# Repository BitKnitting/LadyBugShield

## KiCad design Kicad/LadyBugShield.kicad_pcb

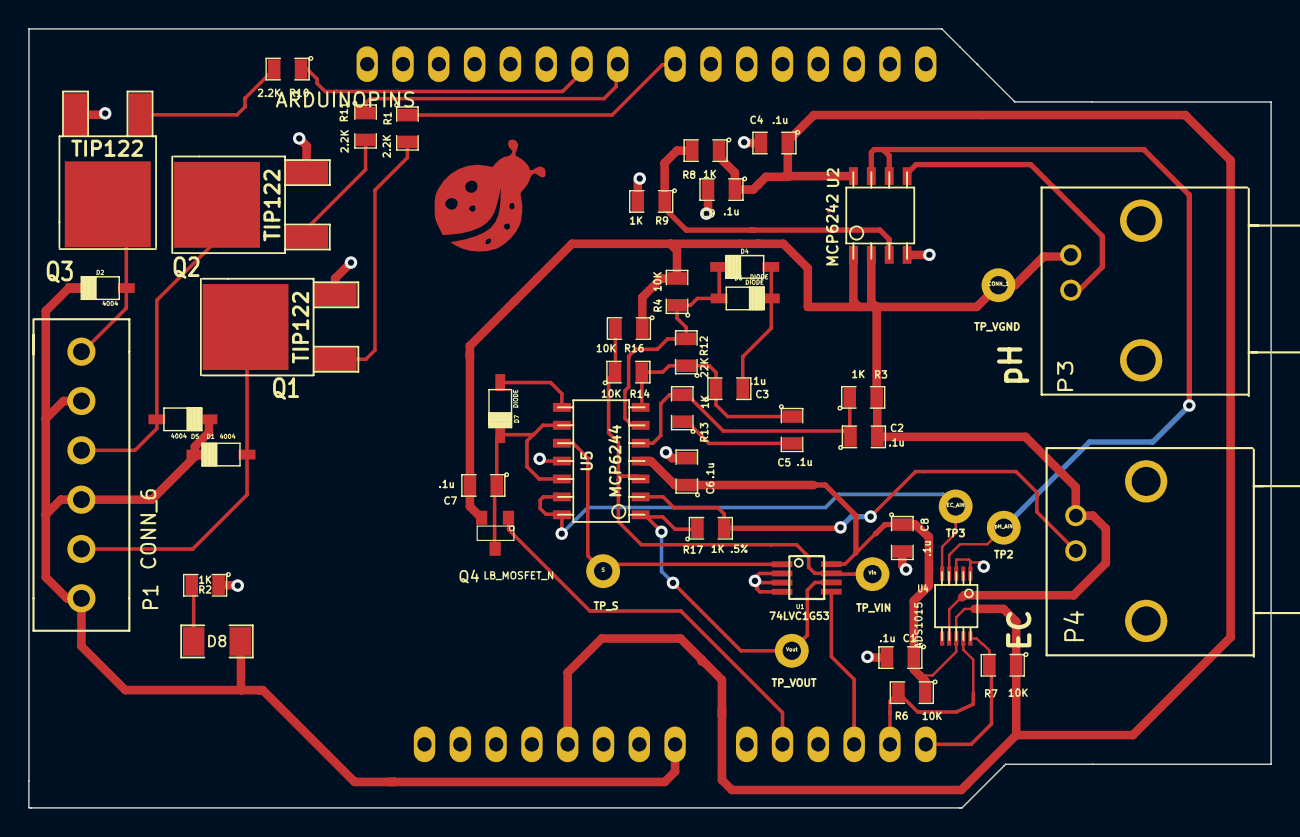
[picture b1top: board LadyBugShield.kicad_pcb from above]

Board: 2 copper layers, 88.1 x 55.3 mm, 49 parts (0 on the bottom side), 33 nets.

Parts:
ARD1: ARDUINOPINS; ArduinoLettuceBuddy
C1, C2, C3, C4, C5, C6, C7, C8, C9: .1u; SM0805
D1, D2, D5: 4004; SOD-123
D4, D6, D7: DIODE; SOD-123
D8: LED; SM1206
P1: CONN_6; LB_CONN_6
P3, P4: BNC; LB_BNC
Q1, Q2, Q3: TIP122; DPAK2
Q4: LB_MOSFET_N; LB_MOSFET
R1, R10, R11: 2.2K; SM0805
R2, R3, R8, R9, R13: 1K; SM0805
R4, R6, R7, R14, R16: 10K; SM0805
R12: 22K; SM0805
R17: 1K .5%; SM0805
TP2: pH_AIN; LB_TestPoint
TP3: EC_AIN; LB_TestPoint
TP_S: S; LB_TestPoint
TP_VGND: CONN_1; LB_TestPoint
TP_VIN: Vin; LB_TestPoint
TP_VOUT: Vout; LB_TestPoint
U1: 74LVC1G53; LB_TSSOP8
U2: MCP6242; so-8
U4: ADS1015; msoic-10
U5: MCP6244; LB_MCP6244

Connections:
/Arduino/12V: ARD1.4, D1.2, D2.2, D5.2, D8.1, P1.1, P1.3, P1.5
/Arduino/FET_pin: ARD1.6, Q4.G
/Arduino/MUX_out_pin: ARD1.8, U1.5
/Arduino/SCL: ARD1.10, R7.2, U4.10
/Arduino/SDA: ARD1.9, R6.2, U4.9
/Arduino/pump1_pin: ARD1.18, R1.1
/Arduino/pump2_pin: ARD1.19, R11.1
/Arduino/pump3_pin: ARD1.20, R10.1
/DigitalAccess/EC_AIN: TP3.1, U4.5, U5.13, U5.14
/DigitalAccess/pH_AIN: TP2.1, U2.6, U2.7, U4.4
/EC/AC/EC_Vin: R14.1, R16.2, TP_VIN.1, U1.7, U5.3
/EC/AC/G1: C3.2, D4.1, D6.2
/EC/AC/W_Vin+: C2.1, R3.1, R13.2, U5.5
/EC/AC/W_Vin-: D4.2, D6.1, R4.1, R12.2, U5.6
/EC/AC/W_Vout: C3.1, C5.1, R12.1, R14.2, U5.7
/EC/AC/f1: C5.2, R13.1
/EC/ECGain/EC_Vout: R17.1, TP_VOUT.1, U1.6, U5.1
/EC/EC_ProbeIN: P4.1, R17.2, U5.2
/EC/Rectify/RVin-: C7.1, D7.2, Q4.D, U5.9, U5.12
/EC/Rectify/R_Vout: D7.1, U5.8
/EC/Rectify/Signal: TP_S.1, U1.1, U5.10
/Power/VGND_V+: R8.2, R9.1, U2.3
/Pumps/pump1: D1.1, P1.2, Q1.2
/Pumps/pump2: D5.1, P1.4, Q2.2
/Pumps/pump3: D2.1, P1.6, Q3.2
/pH/pH_ProbeIN: P3.1, U2.5
GND: ARD1.2, ARD1.3, C1.2, C4.2, C6.2, C8.2, C9.2, Q1.3, Q2.3, Q3.3, R2.1, R9.2, U1.2, U1.3, U1.4, U2.4, U4.1, U4.3, U5.11
unnamed: D8.2, R2.2
unnamed: Q1.1, R1.2
unnamed: Q2.1, R11.2
unnamed: Q3.1, R10.2
VGND: C2.2, C7.2, P3.2, P4.2, Q4.S, R3.2, R4.2, R16.1, TP_VGND.1, U2.1, U2.2, U4.7
Vclean: ARD1.1, C1.1, C4.1, C6.1, C8.1, C9.1, R6.1, R7.1, R8.1, U1.8, U2.8, U4.8, U5.4

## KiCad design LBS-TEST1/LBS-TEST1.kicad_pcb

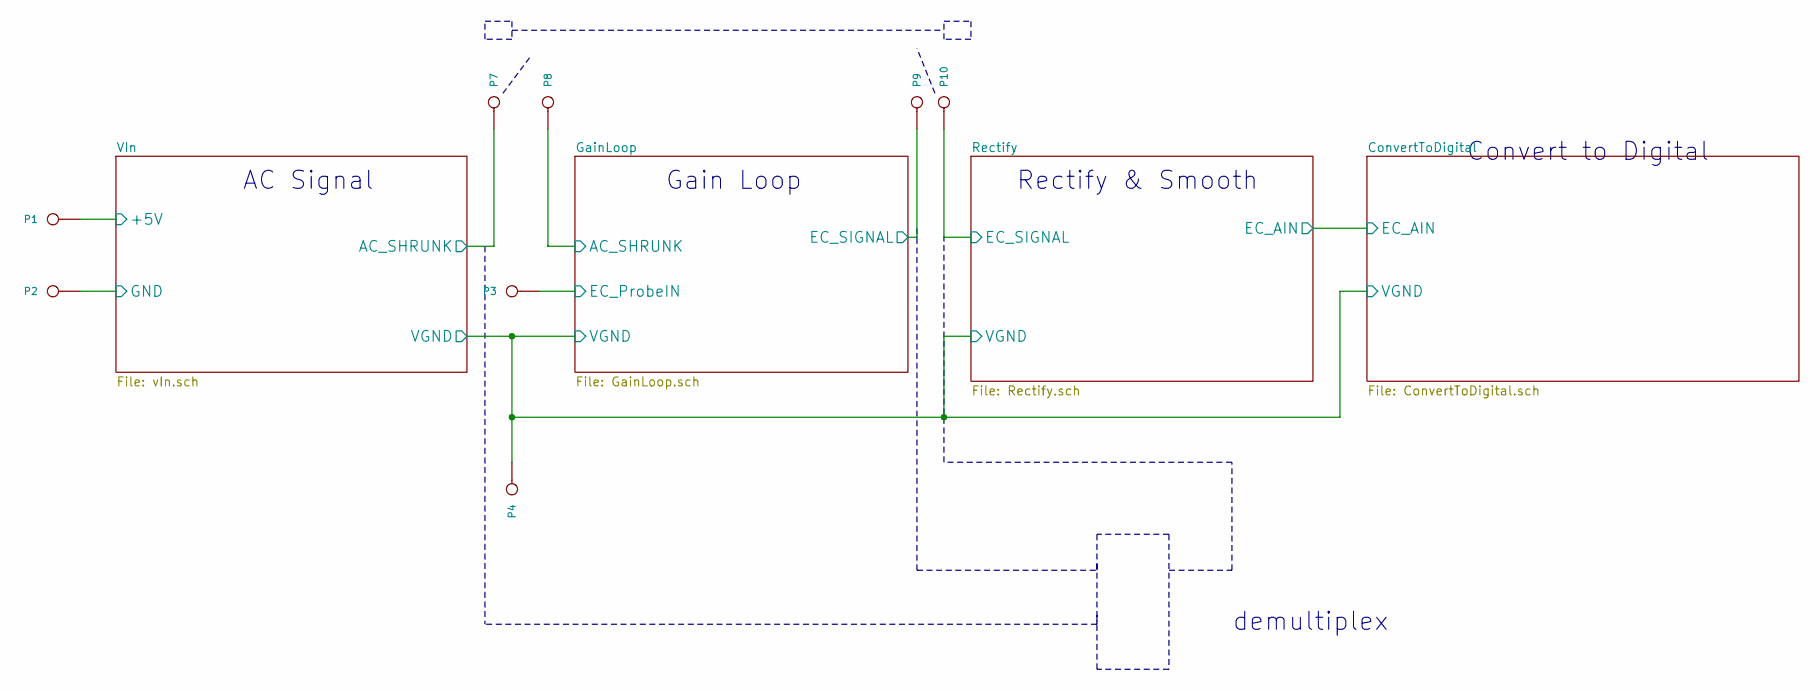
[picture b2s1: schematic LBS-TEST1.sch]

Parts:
P1, P2, P3, P4, P7, P8, P9, P10: CONN_1

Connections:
5+V: P1.1; also elsewhere on the board
/ConvertToDigital/VGND: P4.1; also elsewhere on the board
/GainLoop/AC_SHRUNK: P8.1; also elsewhere on the board
/GainLoop/EC_ProbeIN: P3.1; also elsewhere on the board
/GainLoop/EC_SIGNAL: P9.1; also elsewhere on the board
/Rectify/EC_SIGNAL: P10.1; also elsewhere on the board
/VIn/AC_SHRUNK: P7.1; also elsewhere on the board
PGND: P2.1; also elsewhere on the board

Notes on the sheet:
AC Signal
Gain Loop
Rectify & Smooth
Convert to Digital
demultiplex

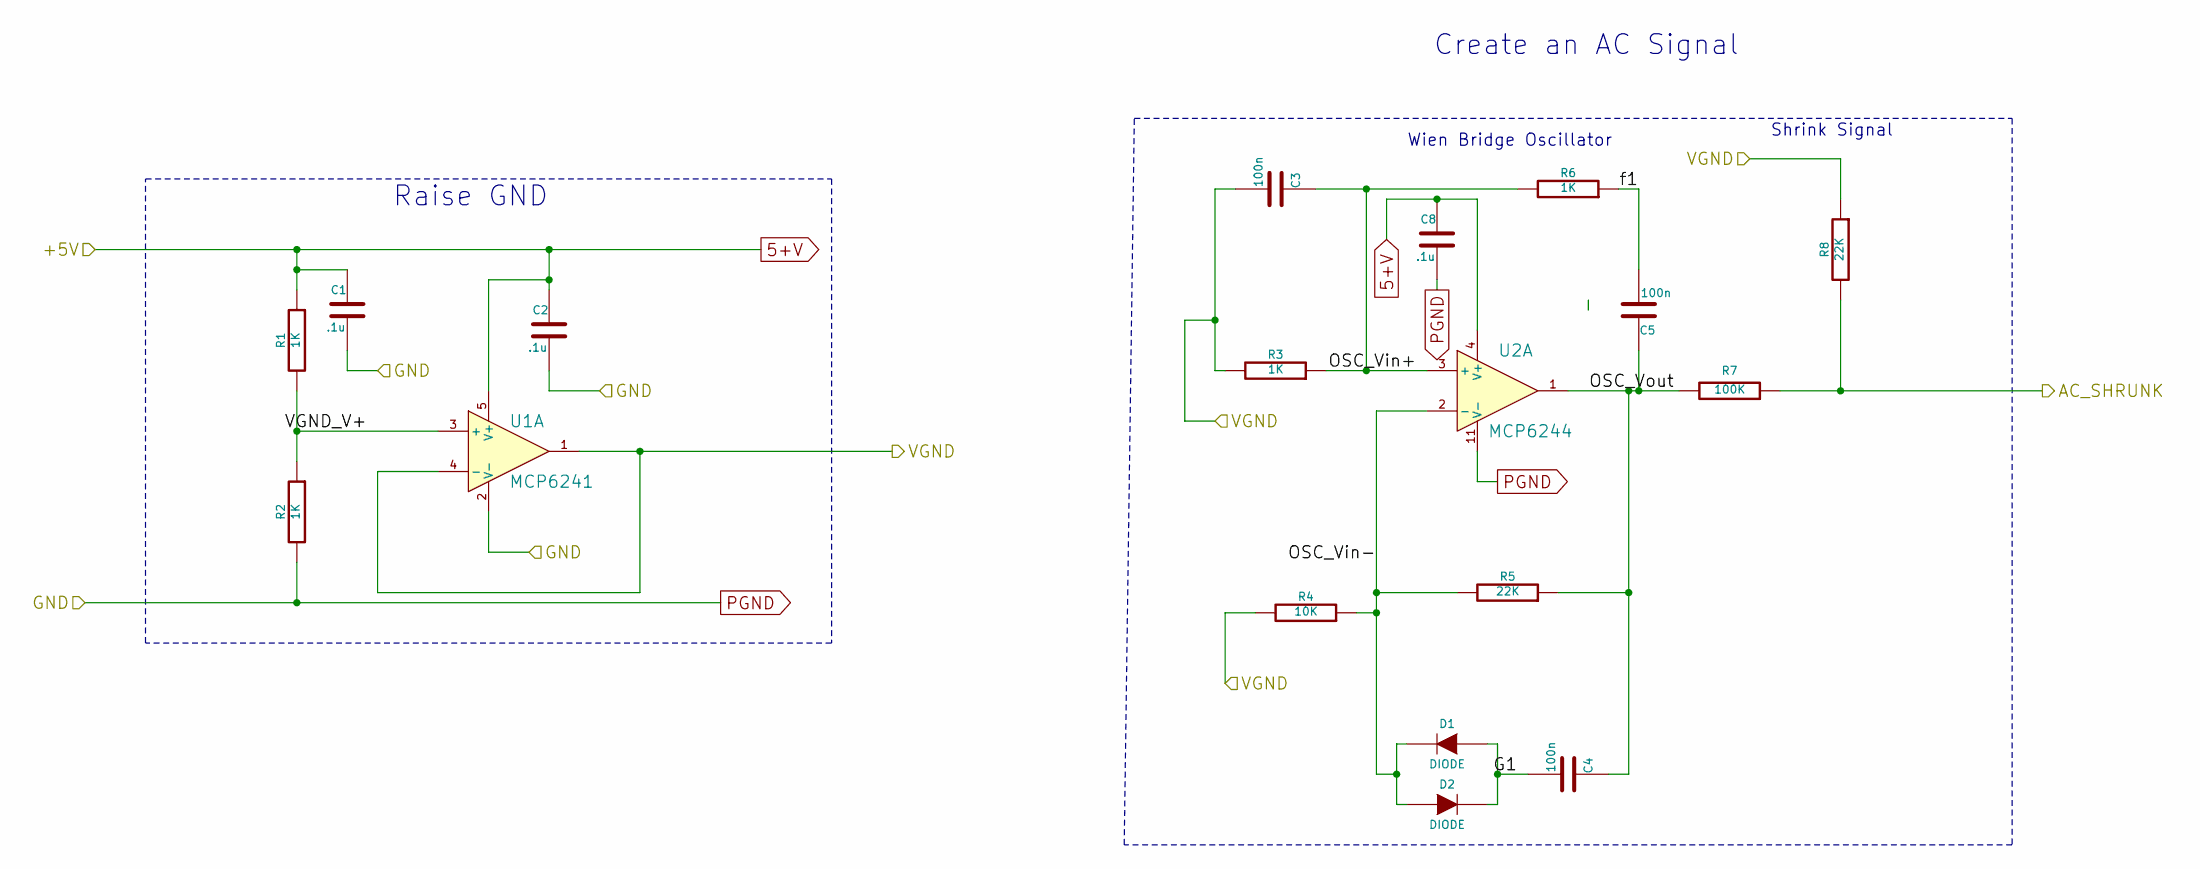
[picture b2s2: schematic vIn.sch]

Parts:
C1, C2, C8: .1u
C3, C4, C5: 100n
D1, D2: DIODE
R1, R2, R3, R6: 1K
R4: 10K
R5, R8: 22K
R7: 100K
U1: MCP6241
U2: MCP6244

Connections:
5+V: C1.1, C2.1, C8.1, R1.1, U1.5 (V+), U2.4 (V+); also elsewhere on the board
/ConvertToDigital/VGND: C3.2, R3.2, R4.2, R8.1, U1.1, U1.4 (-); also elsewhere on the board
/VIn/AC_SHRUNK: R7.1, R8.2; also elsewhere on the board
/VIn/G1: C4.2, D1.1 (A), D2.2 (K)
/VIn/OSC_Vin+: C3.1, R3.1, R6.2, U2.3 (+)
/VIn/OSC_Vin-: D1.2 (K), D2.1 (A), R4.1, R5.2, U2.2 (-)
/VIn/OSC_Vout: C4.1, C5.1, R5.1, R7.2, U2.1
/VIn/VGND_V+: R1.2, R2.1, U1.3 (+)
/VIn/f1: C5.2, R6.1
PGND: C1.2, C2.2, C8.2, R2.2, U1.2 (V-), U2.11 (V-); also elsewhere on the board

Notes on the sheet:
Wien Bridge Oscillator
Shrink Signal
Create an AC Signal
Raise GND

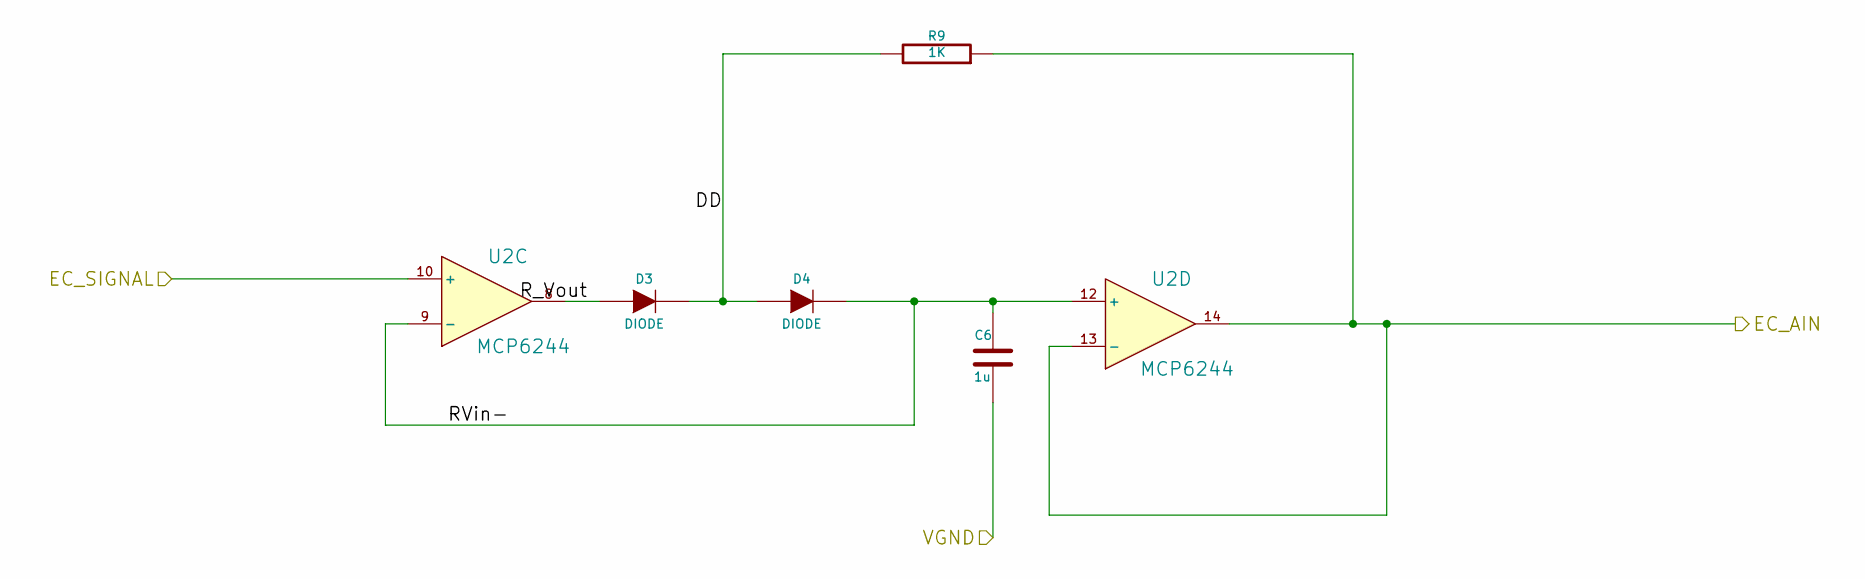
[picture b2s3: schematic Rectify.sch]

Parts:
C6: 1u
D3, D4: DIODE
R9: 1K
U2: MCP6244

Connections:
/ConvertToDigital/EC_AIN: R9.1, U2.13 (-), U2.14
/ConvertToDigital/VGND: C6.2; also elsewhere on the board
/Rectify/DD: D3.2 (K), D4.1 (A), R9.2
/Rectify/EC_SIGNAL: U2.10 (+); also elsewhere on the board
/Rectify/RVin-: C6.1, D4.2 (K), U2.9 (-), U2.12 (+)
/Rectify/R_Vout: D3.1 (A), U2.8

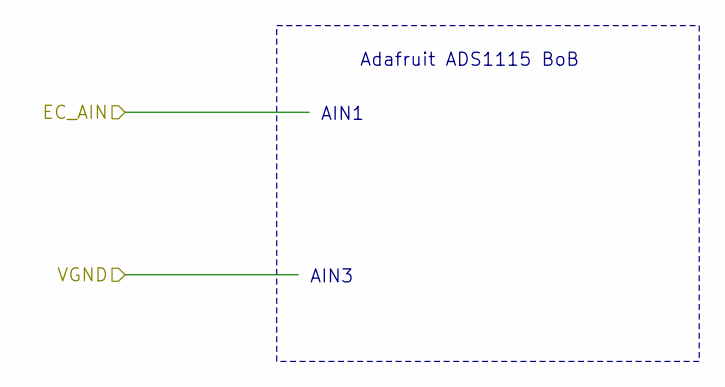
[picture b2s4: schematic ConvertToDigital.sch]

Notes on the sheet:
Adafruit ADS1115 BoB
AIN1
AIN3

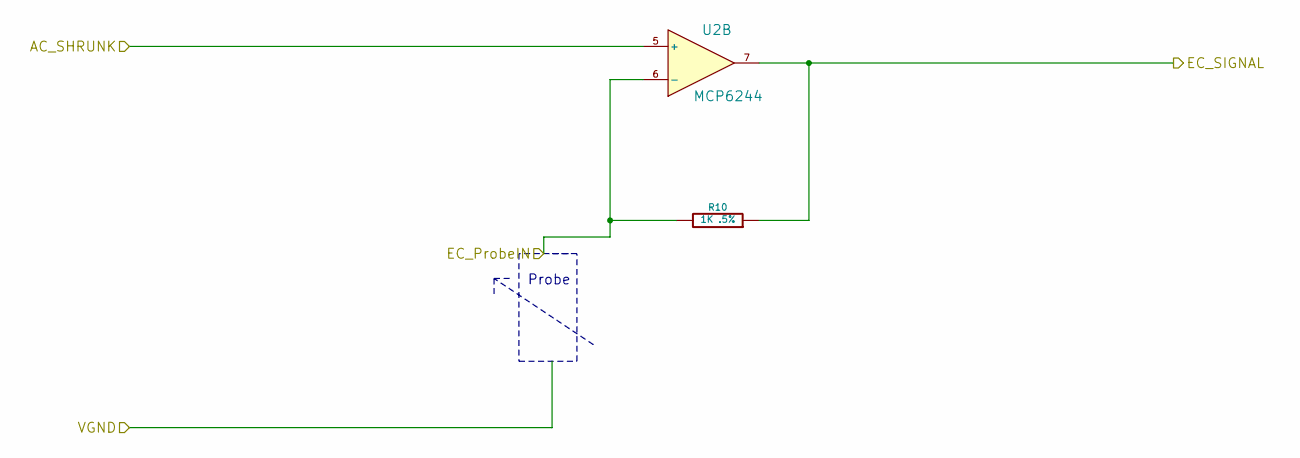
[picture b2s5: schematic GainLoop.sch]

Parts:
R10: 1K .5%
U2: MCP6244

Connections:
/GainLoop/AC_SHRUNK: U2.5 (+); also elsewhere on the board
/GainLoop/EC_ProbeIN: R10.2, U2.6 (-); also elsewhere on the board
/GainLoop/EC_SIGNAL: R10.1, U2.7; also elsewhere on the board

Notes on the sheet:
Probe

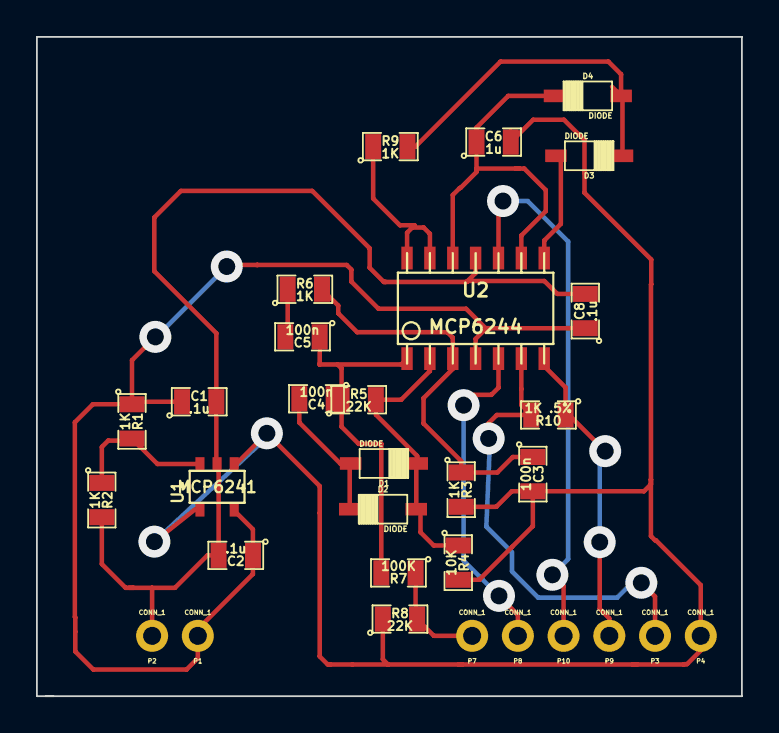
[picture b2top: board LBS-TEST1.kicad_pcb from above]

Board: 2 copper layers, 39.2 x 36.6 mm, 31 parts (0 on the bottom side), 18 nets.

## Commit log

2014-12-18 first pass at layout
2014-12-19 2nd iteration on layout
2014-12-19 update to 2nd pass of layout
2014-12-20 changed diodes added test points
2014-12-21 moved component reference and value for placing components
2014-12-22 added graphics to layout
2014-12-23 changes to layout after 12/22/2014 helpout
2014-12-24 updated layout
2014-12-25 updated to Diode SOD-123 footprint
2014-12-25 added LTSpice files
2014-12-26 added Ladybug logo
2014-12-28 updates based on reviewing layout
2014-12-30 AlphaV1 build that was sent to OshPark
2015-01-15 added LBS-TEST1
2015-01-17 Added Thermistor Arduino Sketch. Changed schematic/layout: label of R15 from 1K to 10K
2015-01-21 fixed BNC connector circuit...still needs final review
2015-01-25 added rectifier sketch
2015-01-26 added switch circuits for rectifier for discussion
2015-01-29 added ECTest Arduino Sketch also updates (not all) to the Schematic
2015-02-01 check in before modifying Layout with updated design
2015-02-02 first pass at new layout
2015-02-07 updating before changing back to master
2015-02-09 layout for Alpha 2
2015-02-09 updated layout to fix wrong footprint for TSSOP8
2015-02-09 updated layout prior to sending to OshPark
2015-02-10 added EC Rectifier Arduino sketch
2015-02-19 added LTSpice model for Red/Royal blue constant current driver
2015-02-26 after pH calibration and read testing
2015-03-23 iPhone app and changes to hw design (not sure I like)
2015-03-24 added nrf8001 data sheet
2015-03-27 Beta 2 sent to OSHPark
2015-04-10 Committing before trying to attempt at adaptive layout in IB
2015-04-10 Looking ok. But want to try out tab bar controller.
2015-04-13 minor changes - all works
2015-04-13 working version
2015-04-13 small changes after 1:1 - beta final
2015-05-02 committing changes before redoing setup view. pretty much everything is working
2015-05-06 First time everything worked.
2015-05-14 shortened length of shield to lower BoM
2015-05-14 shortened length of shield
2015-05-14 updated .gitignore
2015-05-23 First Release
2015-05-27 cleanup
